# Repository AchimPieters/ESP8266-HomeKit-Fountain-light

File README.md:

# ESP8266-HomeKit-Fountain-light
ESP8266 – HomeKit Fountain light

For More Information Visit http://www.studiopieters.nl/

- [x] Make a new NeoPixel Ring
- [x] Beta Testing Software
- [x] Make A PCB
- [x] Ordering PCB Parts
- [x] Beta Testing PCB
- [x] Hardware Installation
- [x] Make POC Movie
- [x] Make end result Movie
- [x] Release KiCad files
- [x] Release gerber files

###### HomeKit Accessory Protocol (HAP) is Apple’s proprietary protocol that enables third-party accessories in the home (e.g., lights, thermostats and door locks) and Apple products to communicate with each other. HAP supports two transports, IP and Bluetooth LE. The information provided in the HomeKit Accessory Protocol Specification (Non-Commercial Version) describes how to implement HAP in an accessory that you create for non-commercial use and that will not be distributed or sold.

###### The HomeKit Accessory Protocol Specification (Non-Commercial Version) can be downloaded from the [HomeKit Apple Developer page.](https://developer.apple.com/homekit/)

###### Copyright © 2019 Apple Inc. All rights reserved.

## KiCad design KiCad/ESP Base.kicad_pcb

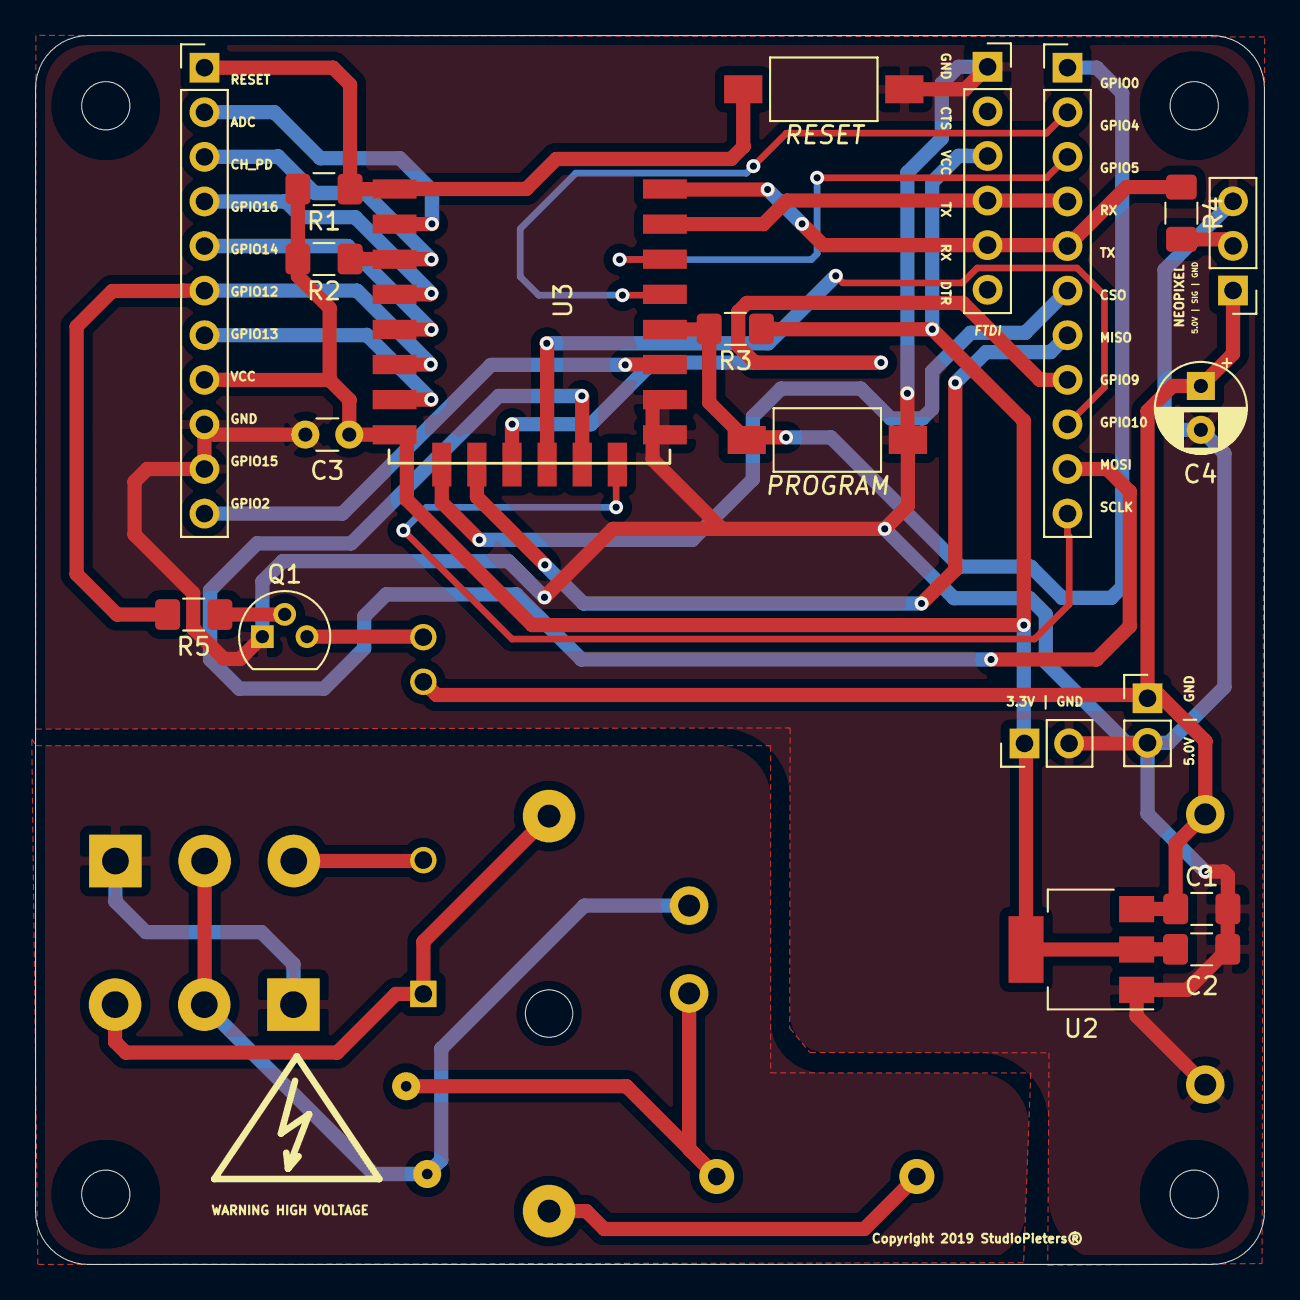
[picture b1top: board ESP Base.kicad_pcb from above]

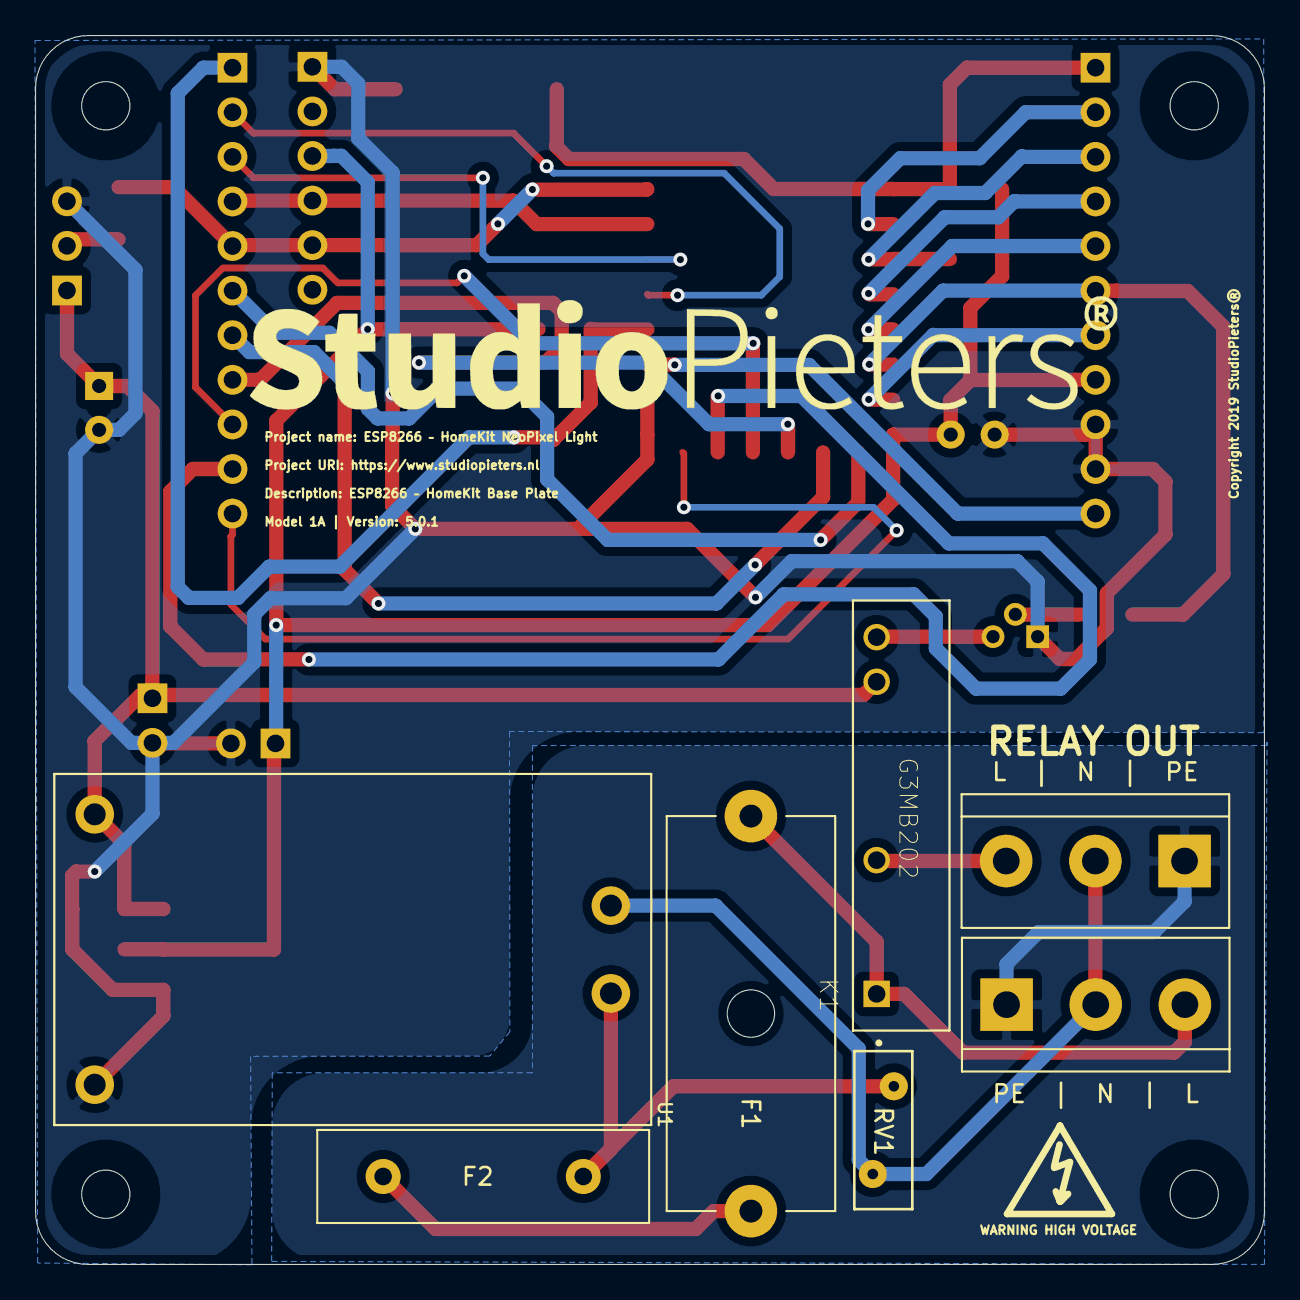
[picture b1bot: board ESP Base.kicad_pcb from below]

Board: 2 copper layers, 70.0 x 70.0 mm, 27 parts (7 on the bottom side), 31 nets.

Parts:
3.3V | GND, 5.0V  |  GND: Conn_01x02; PinHeader_1x02_P2.54mm_Vertical
C1, C2: 10 μF 6,3V; C_1206_3216Metric_Pad1.42x1.75mm_HandSolder
C3: 102; C_Disc_D3.0mm_W1.6mm_P2.50mm
C4: 1000 µF 6.3V; CP_Radial_D5.0mm_P2.50mm
F1: Fuse; Fuseholder_Cylinder-5x20mm_Schurter_0031_8201_Horizontal_Op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
F2: Termal Fuse; Fuse_Littelfuse-LVR100
J1: PE | N | L; TerminalBlock_bornier-3_P5.08mm
J2: NEOPIXEL; PinHeader_1x03_P2.54mm_Vertical
J3: FTDI; PinSocket_1x06_P2.54mm_Vertical
J4, J5: Conn_01x11; PinHeader_1x11_P2.54mm_Vertical
J8: L | N | PE; TerminalBlock_bornier-3_P5.08mm
K1: G3MB202; RELAY_G3MB202PDC12
PROGRAM: PROGRAM; SW_SPST_FSMSM
Q1: 2N2219; TO-92
R1, R2, R3: 10KΩ; R_1206_3216Metric_Pad1.42x1.75mm_HandSolder
R4, R5: 470Ω; R_1206_3216Metric_Pad1.42x1.75mm_HandSolder
RESET: RESET; SW_SPST_FSMSM
RV1: Varistor; RV_Disc_D9mm_W3.3mm_P5mm
U1: HLK-PM01
U2: AMS1117-3.3; SOT-223-3_TabPin2
U3: ESP-12F; ESP-12E_SMD

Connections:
3.3VCC: 3.3V | GND.1, C2.1, C3.1, J3.3, J4.8, R1.2, R2.2, R3.1, U2.2, U3.8
5VCC: 5.0V | GND.1, C1.1, C4.1, J2.1, K1.3, U1.4, U2.3
230V: F1.2, J1.3, K1.1
ADC: J4.2, U3.2
CH_PD: J4.3, R2.1, U3.3
CS0: J5.6, U3.17
Earth_Protective: J1.1, J8.1
GND: 3.3V | GND.2, 5.0V | GND.2, C1.2, C2.2, C3.2, C4.2, J2.3, J3.1, J4.9, J4.10, PROGRAM.1, Q1.1, RESET.1, U1.3, U2.1, U3.9, U3.10
GPIO0: J5.1, PROGRAM.2, R3.2, U3.12
GPIO2: J4.11, U3.11
GPIO4: J5.2, U3.13
GPIO5: J5.3, U3.14
GPIO9: J5.8, U3.19
GPIO10: J5.9, U3.20
GPIO12: J4.6, R5.2, U3.6
GPIO13: J4.7, U3.7
GPIO14: J4.5, U3.5
GPIO16: J4.4, U3.4
MISO: J5.7, U3.18
MOSI: J5.10, U3.21
N: J1.2, J8.2, RV1.2, U1.2
unnamed: F1.1, F2.2
unnamed: F2.1, RV1.1, U1.1
unnamed: J2.2, R4.2
unnamed: J8.3, K1.2
unnamed: K1.4, Q1.3
unnamed: Q1.2, R5.1
RESET: J4.1, R1.1, RESET.2, U3.1
RX: J3.4, J5.4, U3.15
SCLK: J5.11, U3.22
TX: J3.5, J5.5, R4.1, U3.16

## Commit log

2019-08-28 Rotation
2022-03-11 Update Makefile

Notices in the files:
KiCad/ESP Base.kicad_pcb:
Copyright 2019 StudioPieters®
README.md:
License: MIT
